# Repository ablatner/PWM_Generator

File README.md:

PWM Generator for powering servos and motor controllers.

By Team 100

Programming by Andrew Blatner

Electronics by Ethan Anderson

Uses the servo library to make PWM signals for input to servos and motor controllers

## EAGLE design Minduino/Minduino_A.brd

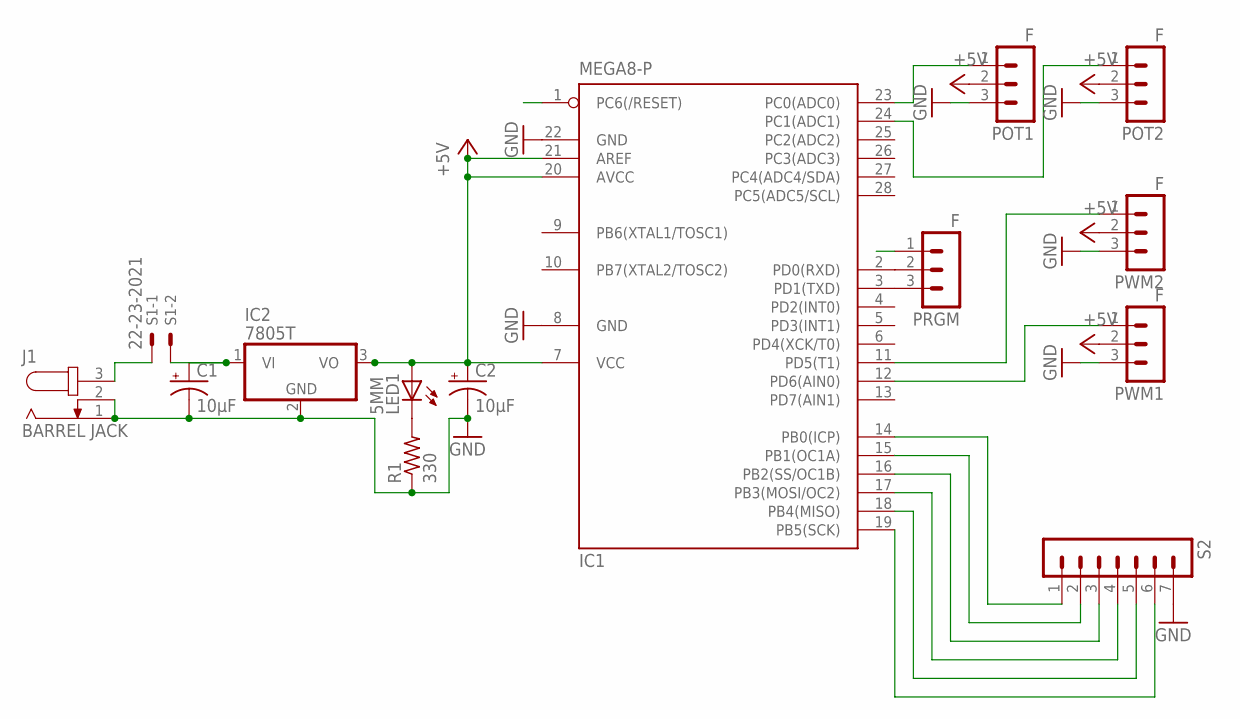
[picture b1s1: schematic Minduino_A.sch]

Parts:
C1, C2: 10µF; E2,5-5
IC1: MEGA8-P; DIL28-3
IC2: 7805T; TO220H
J1: BARREL JACK; SPC4078
LED1: 5MM; LED5MM
POT1, POT2: F; MA03-1
PRGM: F; MA03-1
PWM1, PWM2: F; MA03-1
R1: 330; 0204/5
S1: 22-23-2021
S2: MA07-1

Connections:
+5V: C2.+, IC1.7 (VCC), IC1.20 (AVCC), IC1.21 (AREF), IC2.3 (VO), LED1.A, POT1.2, POT2.2, PWM1.2, PWM2.2
GND: C1.-, C2.-, IC1.8 (GND), IC1.22 (GND), IC2.2 (GND), J1.1, J1.2, POT1.3, POT2.3, PWM1.3, PWM2.3, R1.1, S2.7
unnamed: IC1.12 (PD6(AIN0)), PWM1.1
unnamed: LED1.K (C), R1.2
unnamed: IC1.11 (PD5(T1)), PWM2.1
unnamed: IC1.14 (PB0(ICP)), S2.1
unnamed: C1.+, IC2.1 (VI), S1.2
unnamed: IC1.23 (PC0(ADC0)), POT1.1
unnamed: IC1.24 (PC1(ADC1)), POT2.1
unnamed: IC1.15 (PB1(OC1A)), S2.2
unnamed: IC1.16 (PB2(SS/OC1B)), S2.3
unnamed: IC1.17 (PB3(MOSI/OC2)), S2.4
unnamed: IC1.18 (PB4(MISO)), S2.5
unnamed: IC1.19 (PB5(SCK)), S2.6
unnamed: J1.3, S1.1
unnamed: IC1.2 (PD0(RXD)), PRGM.2
unnamed: IC1.3 (PD1(TXD)), PRGM.3
RST: IC1.1 (PC6(/RESET)), PRGM.1

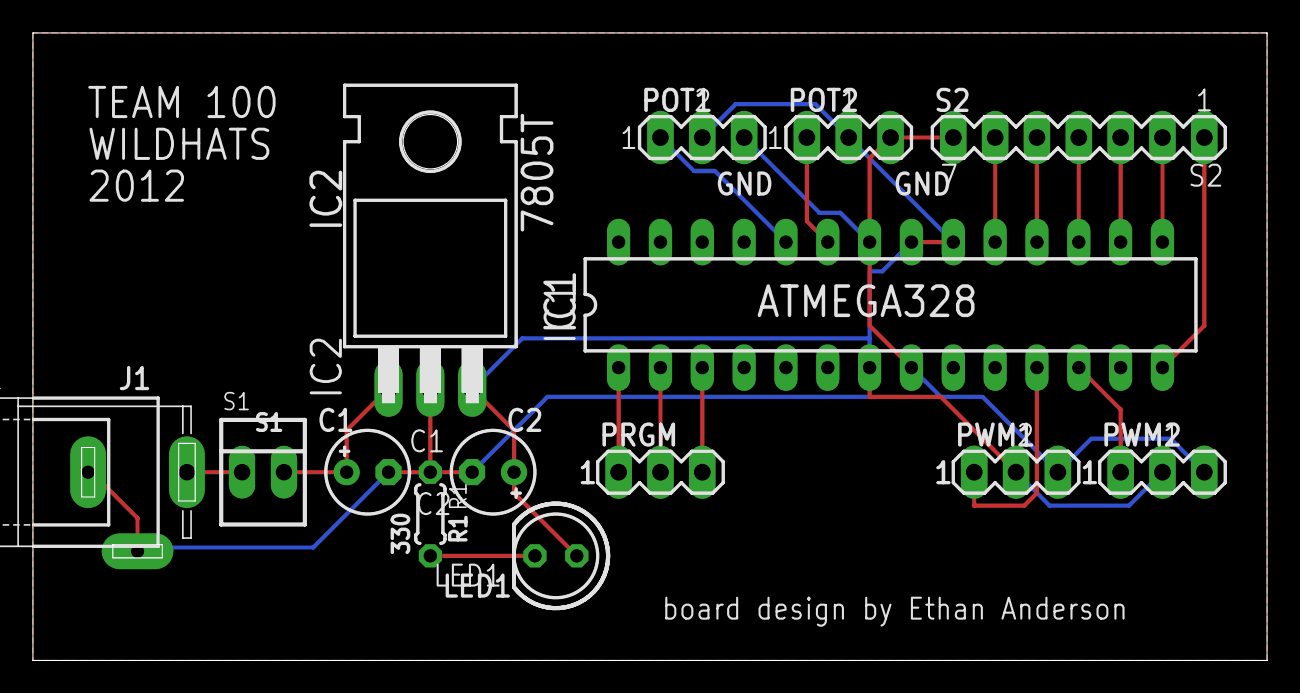
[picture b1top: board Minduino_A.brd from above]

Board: 2 copper layers, 74.9 x 38.1 mm, 14 parts (0 on the bottom side), 18 nets.

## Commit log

2012-08-05 Work from boot camp prep session
2012-08-05 Add Ethan's schematic; move code from subfolder
    Silly Arduino IDE making a subfolder...
2012-08-05 Restructered a ton, clearer, made for 2 outputs
    Put everything into blocks where each action is done for each output at
    once.
    Made better data ouput for debugging.
2012-08-06 Added Circuit Schematic.png
    Made in Eagle by Ethan
2012-08-06 Added README.md
2012-08-06 Added LICENSE.md
2012-08-09 Added reading of mode switch
    Formatting change to README
2012-08-10 Made mode selection better
    Added ModePins.h for mode enumerator
2012-08-11 Continued mode switching
    Fixed ModePins.h indenting and start/endpin values.
    Added todo.txt
    Will probably later change the modes to 3 switches
2012-08-12 Added Ethan's Eagle files
    Still working on code
2012-08-12 Eagle made this when I opened it
2012-08-12 Added .zip to .gitignore
2012-08-12 Changed modes again, back to 1 switch
2012-08-19 Added smoothing, signum function header
    New line at end of ModePins.h
    Set variables so outputs start at neutral position/speed.
    Changed mapping to 0-181 so that it'd be more common to be full forward
    than a smidge less.
    Sets lastOutput.
    Removed braces in single line if-statements
2012-08-19 Moved serial data printing to one spot
    Note: Using data printing causes pausing in smoothing, use higher
    intervals for printing
2012-09-12 No checking for servo mode, made sweep work
    Servo mode messes it up, possibly reading pin 13 doesn't work right
2012-09-12 Added expanded neutral position
2012-09-12 Commented out debugging printing
2012-09-15 Comments explaining sweep function and pullups
2012-09-15 Tried sweep using modulo
    made sweep vars more flexible
2012-09-23 Added silkscreen images
2012-11-21 Added talon selector, many efficiency changes
    Made some variables const
    Heavily commented sweep function
    Removed unused modulo based sweep
2012-11-23 Fixed spacing in README.md
2013-01-04 Moved circuit images to separate folder
    Cleans stuff up
2013-01-04 Version for non-rotary mode switches
2013-01-04 Deleted alt switches, not big enough changes
2013-01-04 Optimizations, clarity
    Moved some things, eg. put similar variable declarations next to each
    other.
    Better explained sweep formula.
    Changed smoothing from absolute value less than positive to raw value
    between negative and positive, uses less memory.
2013-01-07 Made changes to match completed and built design
    Changed max change rate
    Fixed talon switch logic, initializes so last state is always opposite
    current state; that way it attaches the servos correctly.
    Talon pin part of pin enumerator
    Mode switch initializes to independent
    Pin 13 now uses external pull down resistor instead of internal pull up;
2013-01-07 Small changes
    Minimum sweep time changed to 3 seconds, added talon pin to mode switch
    initialization.
    Mapping from 0 to 181, doesn't seem to include high end of range, but
    one below
2013-01-07 Optimizations
    Doubles instead of floats.
    Single time variable instead of calling millis() in several functions.
    Removed passing some globals as a parameter.
2014-01-06 Removed serial.begin() during normal operation
